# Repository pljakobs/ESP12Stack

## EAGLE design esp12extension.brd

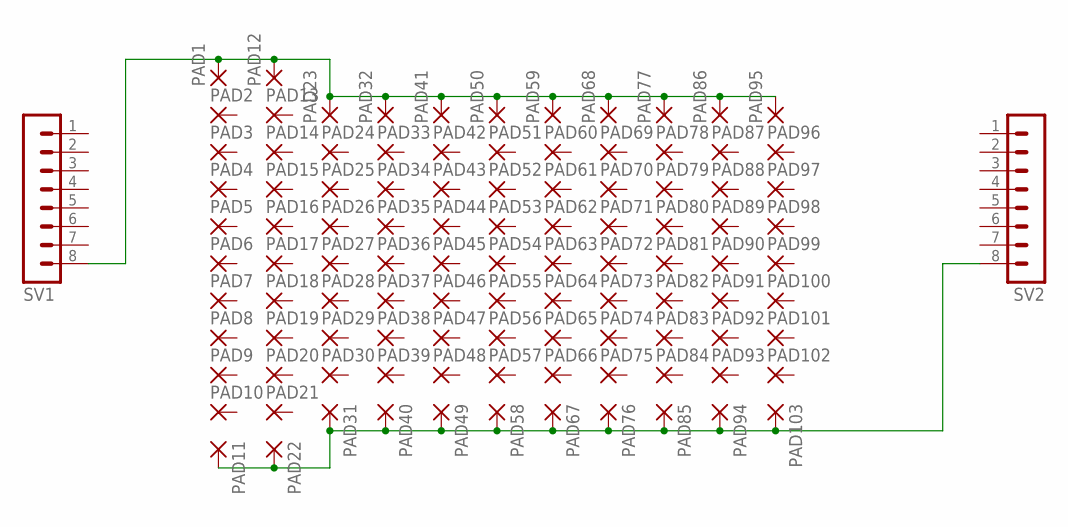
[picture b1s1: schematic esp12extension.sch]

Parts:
PAD1, PAD2, PAD3, PAD4, PAD5, PAD6, PAD7, PAD8, PAD9, PAD10, PAD11, PAD12, PAD13, PAD14, PAD15, PAD16, PAD17, PAD18, PAD19, PAD20, PAD21, PAD22, PAD23, PAD24, PAD25, PAD26, PAD27, PAD28, PAD29, PAD30, PAD31, PAD32, PAD33, PAD34, PAD35, PAD36, PAD37, PAD38, PAD39, PAD40, PAD41, PAD42, PAD43, PAD44, PAD45, PAD46, PAD47, PAD48, PAD49, PAD50, PAD51, PAD52, PAD53, PAD54, PAD55, PAD56, PAD57, PAD58, PAD59, PAD60, PAD61, PAD62, PAD63, PAD64, PAD65, PAD66, PAD67, PAD68, PAD69, PAD70, PAD71, PAD72, PAD73, PAD74, PAD75, PAD76, PAD77, PAD78, PAD79, PAD80, PAD81, PAD82, PAD83, PAD84, PAD85, PAD86, PAD87, PAD88, PAD89, PAD90, PAD91, PAD92, PAD93, PAD94, PAD95, PAD96, PAD97, PAD98, PAD99, PAD100, PAD101, PAD102, PAD103: 1,6/0,8
SV1, SV2: MA08-1

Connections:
GND: PAD11.1, PAD22.1, PAD31.1, PAD40.1, PAD49.1, PAD58.1, PAD67.1, PAD76.1, PAD85.1, PAD94.1, PAD103.1, SV2.8
VCC: PAD1.1, PAD12.1, PAD23.1, PAD32.1, PAD41.1, PAD50.1, PAD59.1, PAD68.1, PAD77.1, PAD86.1, PAD95.1, SV1.8

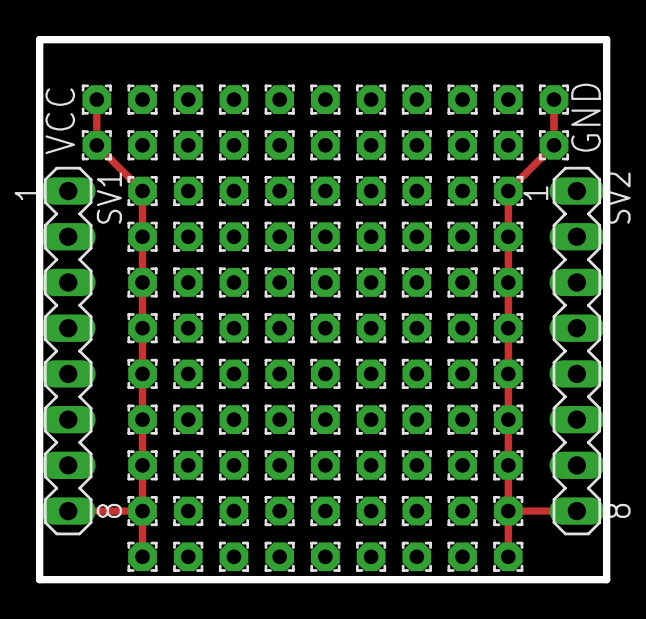
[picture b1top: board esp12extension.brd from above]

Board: 2 copper layers, 31.5 x 30.0 mm, 105 parts (0 on the bottom side), 2 nets.

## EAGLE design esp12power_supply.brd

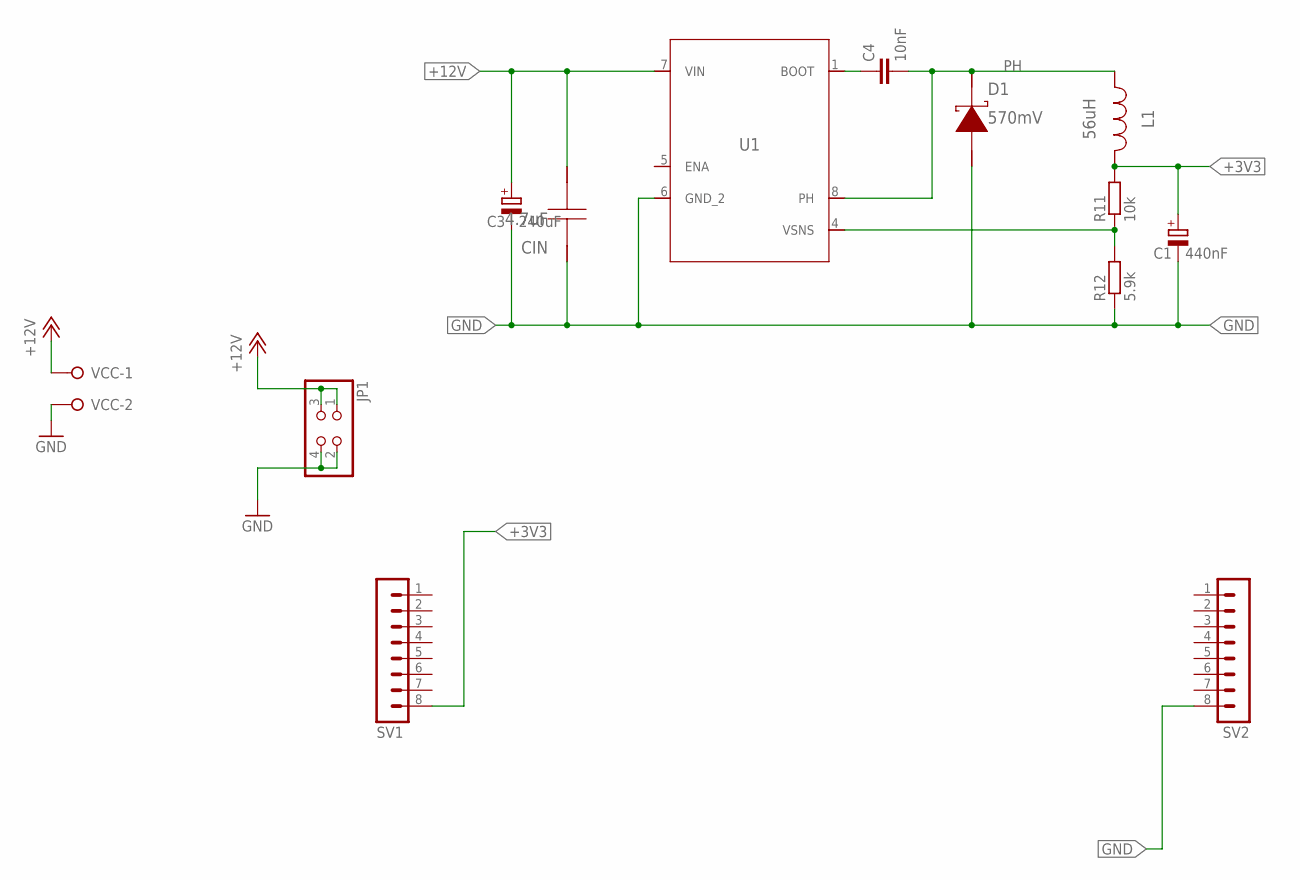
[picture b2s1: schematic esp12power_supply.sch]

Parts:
C1: 440nF; E2,5-7
C3: 240uF; E2,5-7
C4: 10nF; C0805
CIN: 4.7uF; 1206
D1: 570mV; SMA
JP1: PINHD-2X2; 2X02
L1: 56uH; IND_NPI75C
R11: 10k; R0805
R12: 5.9k; R0805
SV1, SV2: MA08-1
U1: TPS5410DR; M08A
VCC: W237-02P; W237-132

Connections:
+3V3: C1.+, L1.1, R11.2, SV1.8
+12V: C3.+, CIN.2, JP1.1, JP1.3, U1.7 (VIN), VCC.1
BOOT: C4.1, U1.1 (BOOT)
GND: C1.-, C3.-, CIN.1, D1.2 (A), JP1.2, JP1.4, R12.1, SV2.8, U1.6 (GND_2), VCC.2
PH: C4.2, D1.1 (K), L1.2, U1.8 (PH)
SENS: R11.1, R12.2, U1.4 (VSNS)

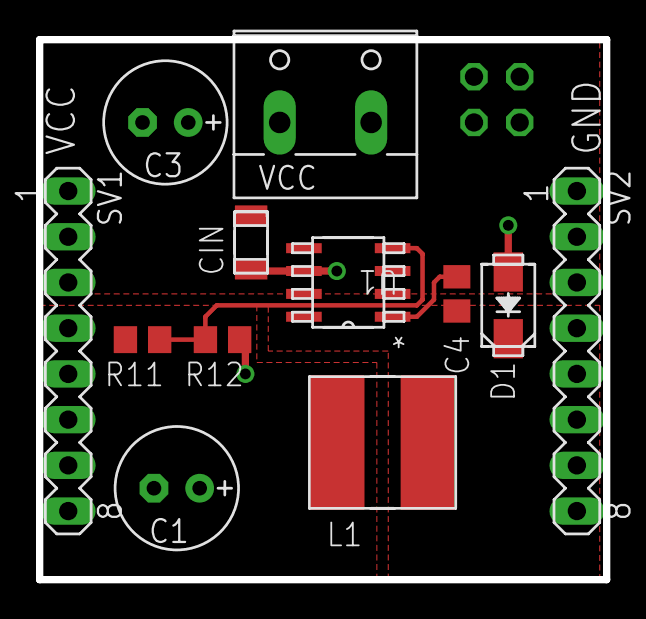
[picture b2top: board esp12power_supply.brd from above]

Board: 2 copper layers, 31.5 x 30.0 mm, 13 parts (1 on the bottom side), 6 nets.

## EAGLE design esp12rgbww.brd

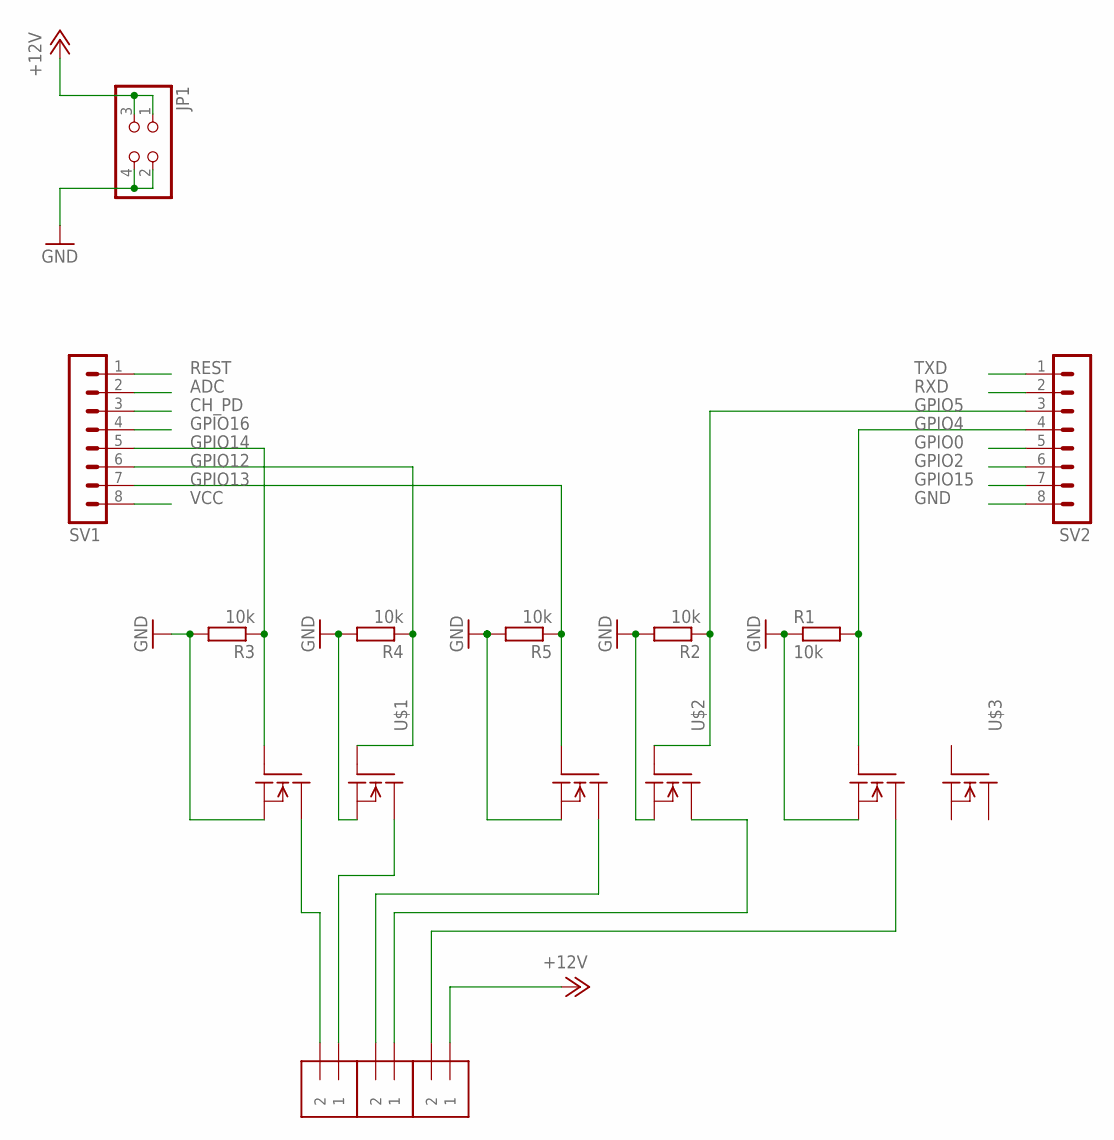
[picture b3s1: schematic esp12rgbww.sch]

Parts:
J1, J2, J3: 1X2-3.5MM
JP1: PINHD-2X2; 2X02
R1, R2, R3, R4, R5: 10k; R0805
SV1, SV2: MA08-1
U$1, U$2, U$3: AOD4806; SO08

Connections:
+12V: J3.1, JP1.1, JP1.3
ADC: SV1.2
B: J1.2, U$1.7 (D1), U$1.8 (D1)
CH_PD: SV1.3
CW: J2.1, U$2.5 (D), U$2.6 (D)
G: J1.1, U$1.5 (D), U$1.6 (D)
GND: JP1.2, JP1.4, R1.1, R2.2, R3.2, R4.2, R5.2, SV2.8, U$1.1 (S1), U$1.3 (S), U$2.1 (S1), U$2.3 (S), U$3.1 (S1)
GPIO0: SV2.5
GPIO2: SV2.6
GPIO4: R1.2, SV2.4, U$3.2 (G1)
GPIO5: R2.1, SV2.3, U$2.4 (G)
GPIO12: R4.1, SV1.6, U$1.4 (G)
GPIO13: R5.1, SV1.7, U$2.2 (G1)
GPIO14: R3.1, SV1.5, U$1.2 (G1)
GPIO15: SV2.7
GPIO16: SV1.4
R: J2.2, U$2.7 (D1), U$2.8 (D1)
REST: SV1.1
RXD: SV2.2
TXD: SV2.1
VCC: SV1.8
WW: J3.2, U$3.7 (D1), U$3.8 (D1)

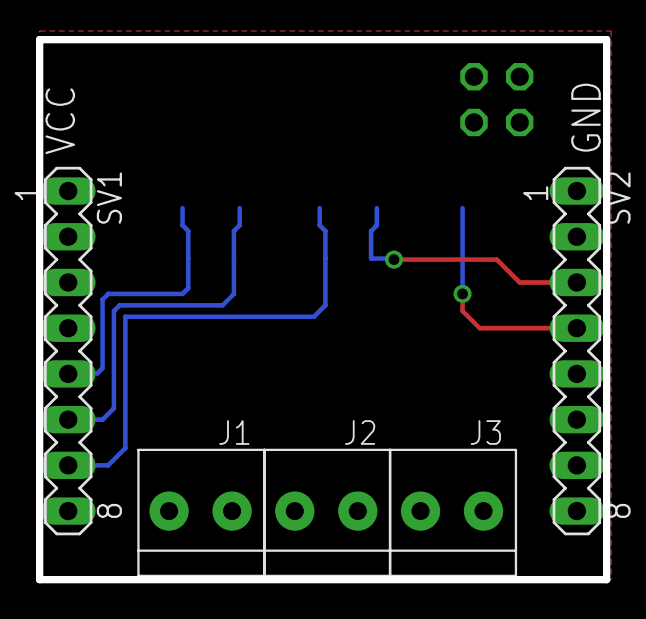
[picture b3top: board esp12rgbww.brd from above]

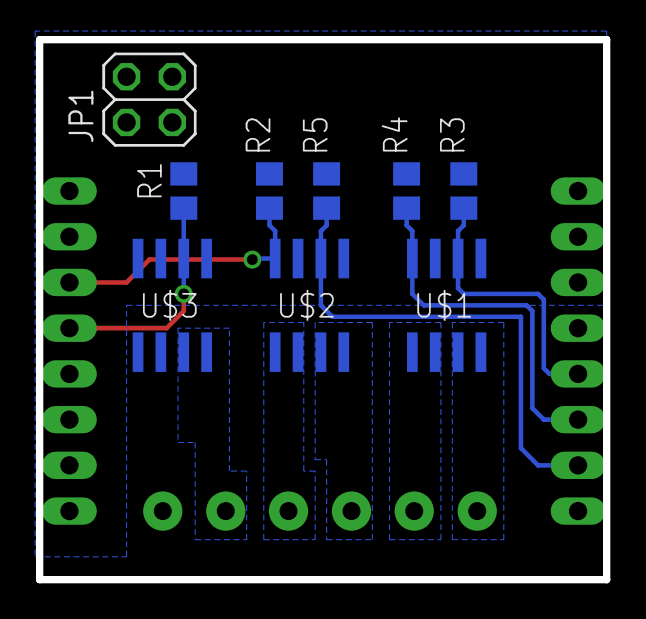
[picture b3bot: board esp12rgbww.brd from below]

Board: 2 copper layers, 31.5 x 30.0 mm, 14 parts (9 on the bottom side), 12 nets.
